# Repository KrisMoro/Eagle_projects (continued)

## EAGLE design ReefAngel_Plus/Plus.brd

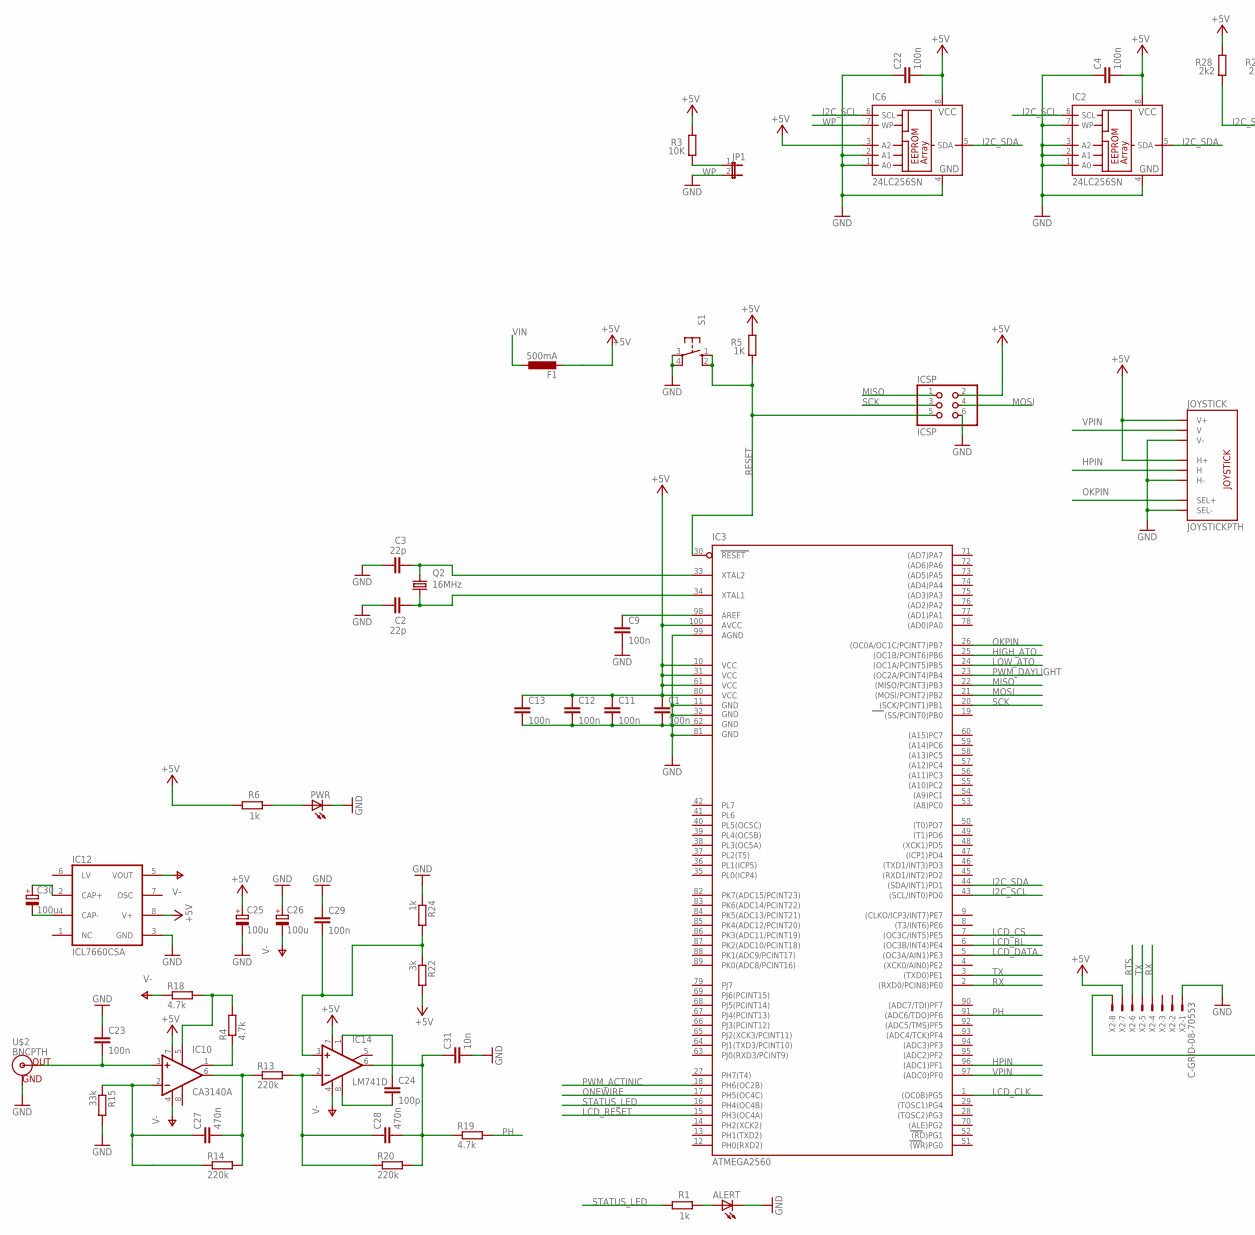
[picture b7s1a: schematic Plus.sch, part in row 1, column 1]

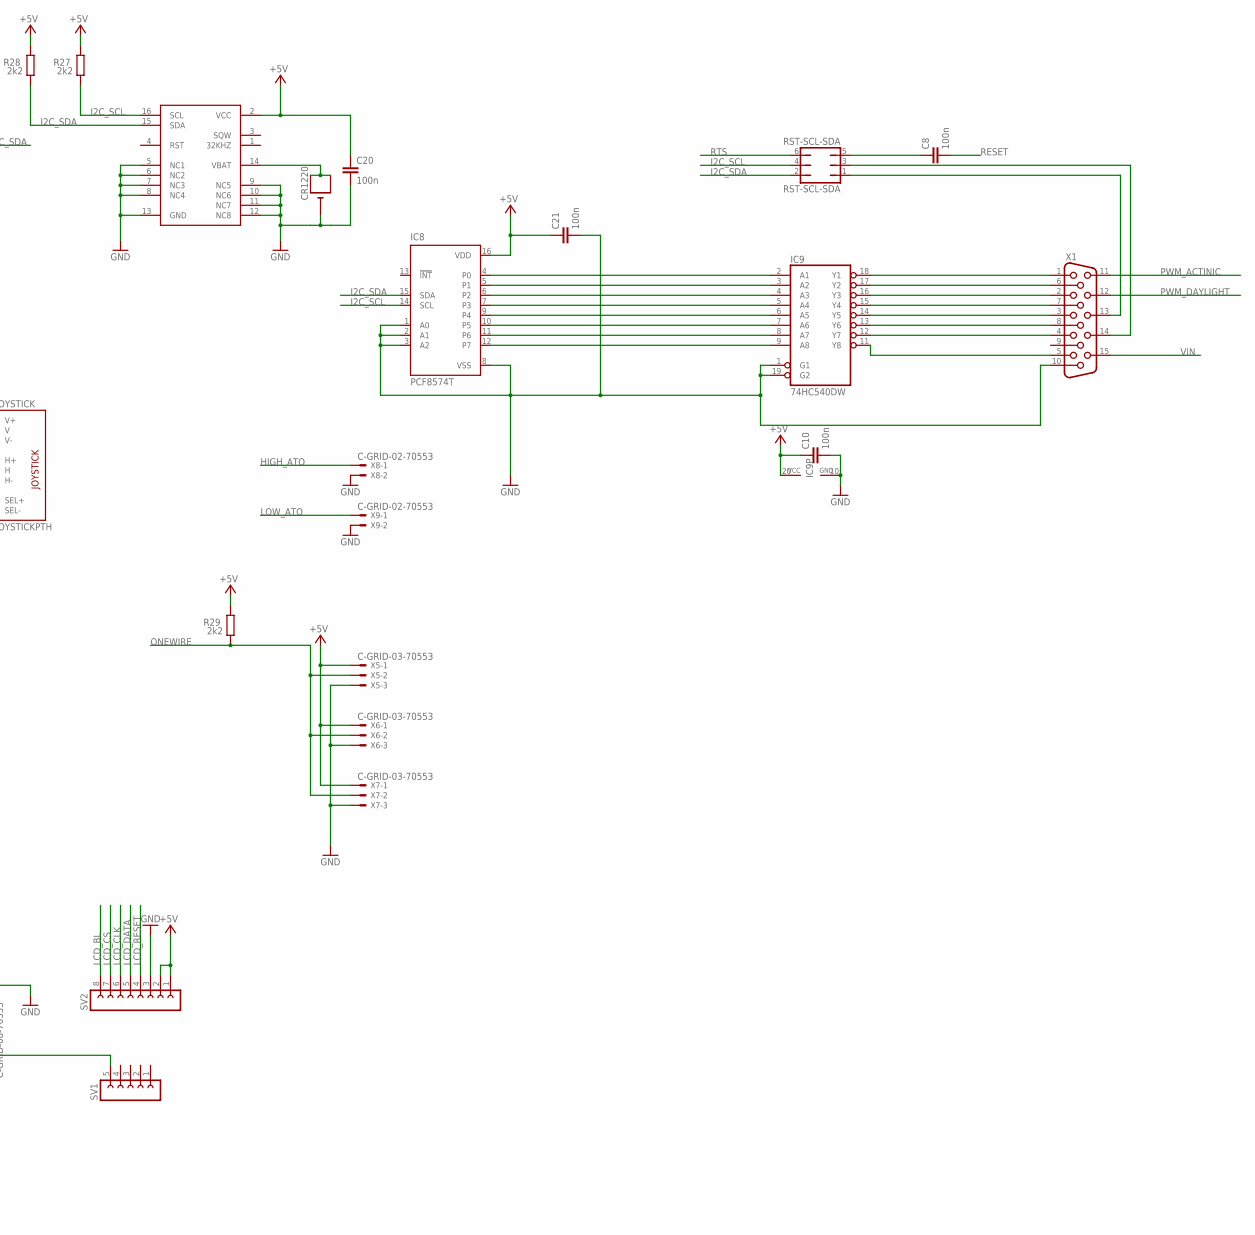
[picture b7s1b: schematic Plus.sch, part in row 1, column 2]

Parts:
ALERT: LED3MM
C1, C4, C8, C9, C10, C11, C12, C13, C20, C21, C22, C23, C29: 100n; C0805
C2, C3: 22p; C0805
C24: 100p; C0805
C25, C26, C30: 100u; PANASONIC_D
C27, C28: 470n; C0805
C31: 10n; C0805
CR1220: CR1220SMT; CR1220-SMD
F1: 500mA; L1812
IC2, IC6: 24LC256SN; SO-08
IC3: ATMEGA2560; TQFP100
IC7: DS3231W; SO16W
IC8: PCF8574T; SO16W
IC9: 74HC540DW; SO20W
IC10: CA3140A; SO08
IC12: ICL7660CSA; SO08
IC14: LM741D; SO08
ICSP: ICSP; 2X03
JOYSTICK: JOYSTICKPTH; JOYSTICK
JP1: JP1E; JP1
PWR: LED3MM
Q2: 16MHz; HC49/S
R1, R6, R24: 1k; R0805
R3: 10K; R0805
R4, R18, R19: 4.7k; R0805
R5: 1K; R0805
R13, R14, R20: 220k; R0805
R15: 33k; R0805
R22: 3k; R0805
R27, R28, R29: 2k2; R0805
RST-SCL-SDA: RST-SCL-SDA; JP3Q
S1: 10-XX; B3F-10XX
SV1: FE05-1
SV2: FE08-1; FE08
U$2: BNCPTH; BNC
X1: HF15H; HDF15H
X2: C-GRID-08-70553; 70553-08
X5, X6, X7: C-GRID-03-70553; 70553-03
X8, X9: C-GRID-02-70553; 70553-02

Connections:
+5V: C1.1, C4.2, C10.1, C11.1, C12.1, C13.1, C20.1, C21.1, C22.2, C25.+, F1.2, IC2.8 (VCC), IC3.10 (VCC), IC3.31 (VCC1), IC3.61 (VCC2), IC3.80 (VCC3), IC3.100 (AVCC), IC6.3 (A2), IC6.8 (VCC), IC7.2 (VCC), IC8.16 (VDD), IC9.20 (VCC), IC10.7 (V+), IC12.8 (V+), IC14.7 (V+), ICSP.2, JOYSTICK.H1 (H+), JOYSTICK.V1 (V+), R3.2, R5.2, R6.1, R22.2, R27.2, R28.2, R29.2, SV2.1, SV2.2, X2.7, X5.1, X6.1, X7.1
GND: ALERT.K (C), C1.2, C2.1, C3.1, C4.1, C9.2, C10.2, C11.2, C12.2, C13.2, C20.2, C21.2, C22.1, C23.1, C25.-, C26.+, C29.1, C31.2, CR1220.-, IC2.1 (A0), IC2.2 (A1), IC2.3 (A2), IC2.4 (GND), IC2.7 (WP), IC3.11 (GND), IC3.32 (GND1), IC3.62 (GND2), IC3.81 (GND3), IC3.99 (AGND), IC6.1 (A0), IC6.2 (A1), IC6.4 (GND), IC7.5 (NC1), IC7.6 (NC2), IC7.7 (NC3), IC7.8 (NC4), IC7.9 (NC5), IC7.10 (NC6), IC7.11 (NC7), IC7.12 (NC8), IC7.13 (GND), IC8.1 (A0), IC8.2 (A1), IC8.3 (A2), IC8.8 (VSS), IC9.1 (G1), IC9.10 (GND), IC9.19 (G2), IC12.3 (GND), ICSP.6, JOYSTICK.B2A (SEL-), JOYSTICK.H3 (H-), JOYSTICK.V3 (V-), JP1.2, PWR.K (C), R15.2, R24.1, S1.3, S1.4 (P1), SV2.3, U$2.GND, X1.10, X2.1, X5.3, X6.3, X7.3, X8.2, X9.2
HIGH_ATO: IC3.25 ((OC1B/PCINT6)PB6), X8.1
HPIN: IC3.96 ((ADC1)PF1), JOYSTICK.H2 (H)
I2C_SCL: IC2.6 (SCL), IC3.43 ((SCL/INT0)PD0), IC6.6 (SCL), IC7.16 (SCL), IC8.14 (SCL), R27.1, RST-SCL-SDA.4
I2C_SDA: IC2.5 (SDA), IC3.44 ((SDA/INT1)PD1), IC6.5 (SDA), IC7.15 (SDA), IC8.15 (SDA), R28.1, RST-SCL-SDA.2
LCD_BL: IC3.6 ((OC3B/INT4)PE4), SV2.8
LCD_CLK: IC3.1 ((OC0B)PG5), SV2.6
LCD_CS: IC3.7 ((OC3C/INT5)PE5), SV2.7
LCD_DATA: IC3.5 ((OC3A/AIN1)PE3), SV2.5
LCD_RESET: IC3.15 (PH3(OC4A)), SV2.4
LOW_ATO: IC3.24 ((OC1A/PCINT5)PB5), X9.1
MISO: IC3.22 ((MISO/PCINT3)PB3), ICSP.1
MOSI: IC3.21 ((MOSI/PCINT2)PB2), ICSP.4
unnamed: C9.1, IC3.98 (AREF)
unnamed: CR1220.+$1 (+), CR1220.+$2 (+1), IC7.14 (VBAT)
unnamed: PWR.A, R6.2
unnamed: C2.2, IC3.34 (XTAL1), Q2.1
unnamed: C3.2, IC3.33 (XTAL2), Q2.2
unnamed: IC9.18 (Y1), X1.1
unnamed: C24.1, IC14.1 (ON1)
unnamed: RST-SCL-SDA.1, X1.13
unnamed: IC9.17 (Y2), X1.6
unnamed: RST-SCL-SDA.3, X1.14
unnamed: IC9.16 (Y3), X1.2
unnamed: IC9.15 (Y4), X1.7
unnamed: IC9.14 (Y5), X1.3
unnamed: IC9.13 (Y6), X1.8
unnamed: IC9.12 (Y7), X1.4
unnamed: IC9.11 (Y8), X1.5
unnamed: IC8.4 (P0), IC9.2 (A1)
unnamed: IC8.5 (P1), IC9.3 (A2)
unnamed: IC8.6 (P2), IC9.4 (A3)
unnamed: IC8.7 (P3), IC9.5 (A4)
unnamed: IC8.9 (P4), IC9.6 (A5)
unnamed: IC8.10 (P5), IC9.7 (A6)
unnamed: IC8.11 (P6), IC9.8 (A7)
unnamed: IC8.12 (P7), IC9.9 (A8)
unnamed: C29.2, IC14.3 (+IN), R22.1, R24.2
unnamed: C30.-, IC12.4 (CAP-)
unnamed: C30.+, IC12.2 (CAP+)
unnamed: C23.2, IC10.3 (+IN), U$2.S (OUT)
unnamed: C24.2, IC14.8 (OPT)
unnamed: C27.2, IC10.6 (OUT), R13.1, R14.2
unnamed: C27.1, IC10.2 (-IN), R14.1, R15.1
unnamed: C8.1, RST-SCL-SDA.5
unnamed: IC10.5 (ON), R4.2, R18.2
unnamed: IC10.1 (ON/CMP), R4.1
unnamed: C28.1, IC14.2 (-IN), R13.2, R20.1
unnamed: C28.2, C31.1, IC14.6 (OUT), R19.1, R20.2
unnamed: ALERT.A, R1.2
unnamed: SV1.5, X2.8
OKPIN: IC3.26 ((OC0A/OC1C/PCINT7)PB7), JOYSTICK.B1A (SEL+)
ONEWIRE: IC3.17 (PH5(OC4C)), R29.1, X5.2, X6.2, X7.2
PH: IC3.91 ((ADC6/TDO)PF6), R19.2
PWM_ACTINIC: IC3.18 (PH6(OC2B)), X1.11
PWM_DAYLIGHT: IC3.23 ((OC2A/PCINT4)PB4), X1.12
RESET: C8.2, IC3.30 (RESET), ICSP.5, R5.1, S1.1 (S), S1.2 (S1)
RTS: RST-SCL-SDA.6, X2.6
RX: IC3.2 ((RXD0/PCIN8)PE0), X2.4
SCK: IC3.20 ((SCK/PCINT1)PB1), ICSP.3
STATUS_LED: IC3.16 (PH4(OC4B)), R1.1
TX: IC3.3 ((TXD0)PE1), X2.5
V-: C26.-, IC10.4 (V-), IC12.5 (VOUT), IC14.4 (V-), R18.1
VIN: F1.1, X1.15
VPIN: IC3.97 ((ADC0)PF0), JOYSTICK.V2 (V)
WP: IC6.7 (WP), JP1.1, R3.1

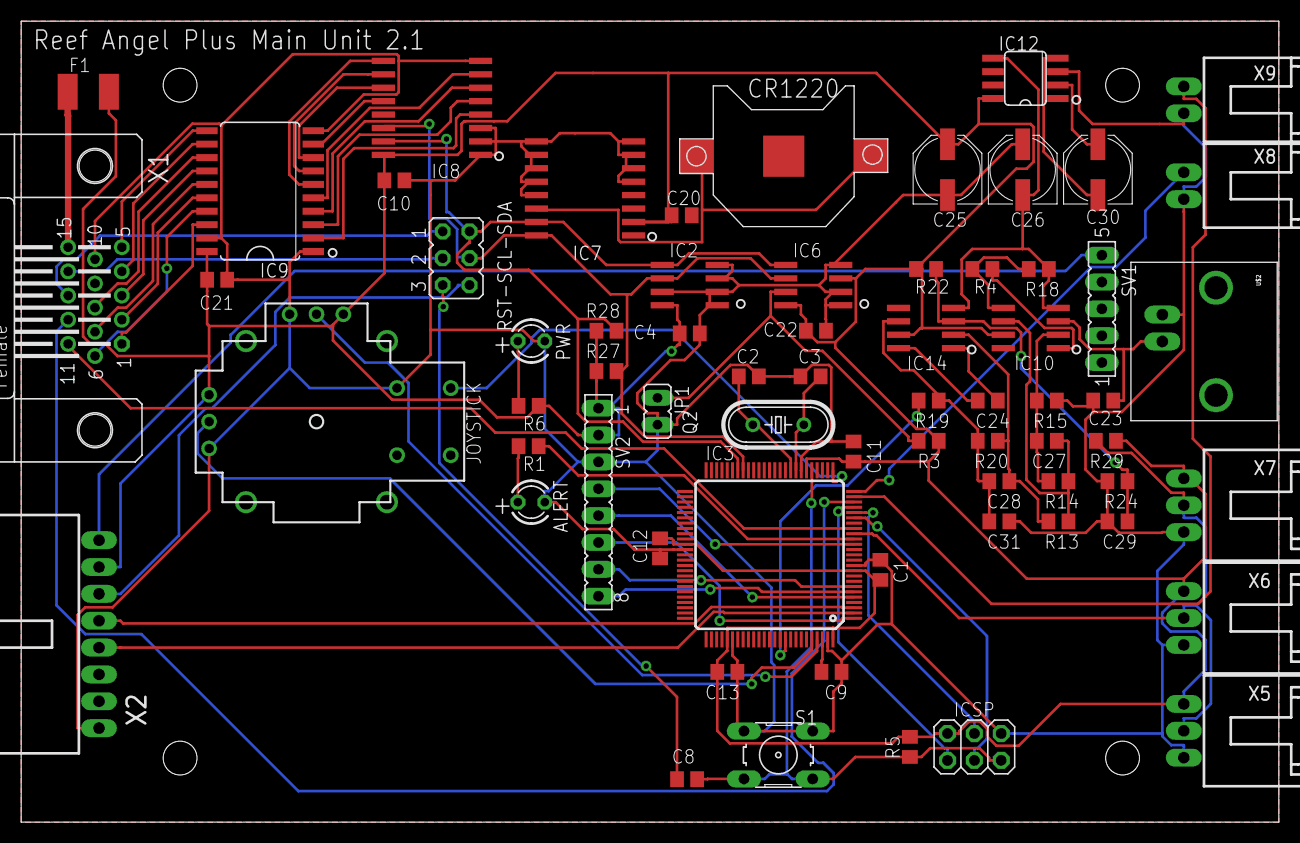
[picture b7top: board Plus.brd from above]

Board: 2 copper layers, 119.0 x 75.8 mm, 67 parts (0 on the bottom side), 67 nets.

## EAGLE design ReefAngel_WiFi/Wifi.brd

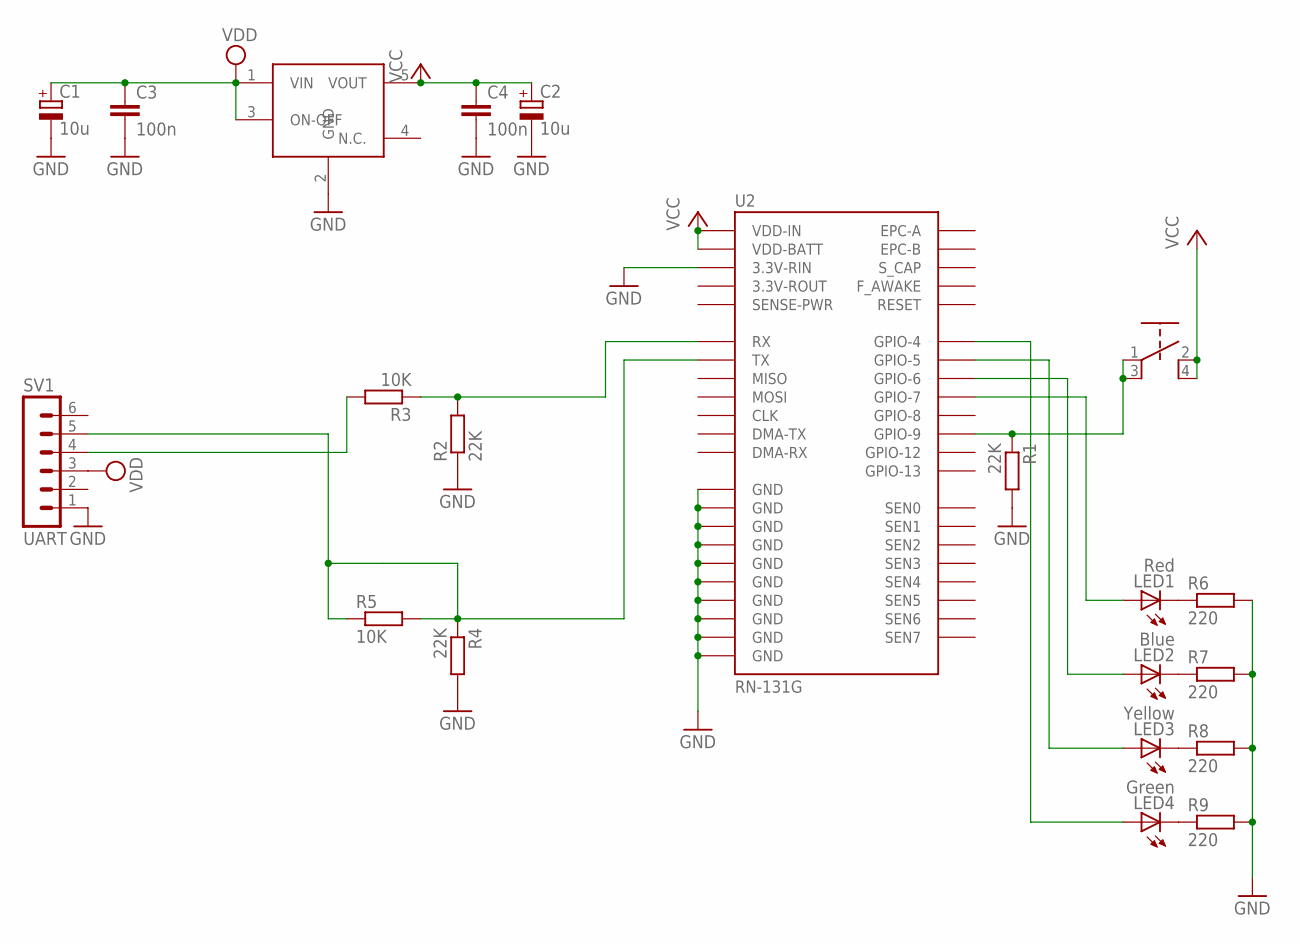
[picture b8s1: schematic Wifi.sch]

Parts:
C1, C2: 10u; A/3216-18W
C3, C4: 100n; C0805
LED1: Red; LED3MM
LED2: Blue; LED3MM
LED3: Yellow; LED3MM
LED4: Green; LED3MM
R1, R2, R4: 22K; R0805
R3, R5: 10K; R0805
R6, R7, R8, R9: 220; R0805
S2: PUSHBUTTON
SV1: UART; MA06-1
U1: LP2985; SOT23-5
U2: RN-131G

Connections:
GND: C1.-, C2.-, C3.2, C4.2, R1.2, R2.1, R4.2, R6.2, R7.2, R8.2, R9.2, SV1.1, U1.2 (GND), U2.P$18 (3.3V-RIN), U2.P$19 (GND), U2.P$36 (GND), U2.P$37 (GND), U2.P$38 (GND), U2.P$39 (GND), U2.P$40 (GND), U2.P$41 (GND), U2.P$42 (GND), U2.P$43 (GND), U2.P$44 (GND)
unnamed: R1.1, S2.1, S2.3, U2.P$24 (GPIO-9)
unnamed: R2.2, R3.1, U2.P$12 (RX)
unnamed: R4.1, R5.1, R5.2, SV1.5, U2.P$13 (TX)
unnamed: LED1.K (C), R6.1
unnamed: R3.2, SV1.4
unnamed: LED2.K (C), R7.1
unnamed: LED3.K (C), R8.1
unnamed: LED4.K (C), R9.1
unnamed: LED1.A, U2.P$26 (GPIO-7)
unnamed: LED2.A, U2.P$27 (GPIO-6)
unnamed: LED3.A, U2.P$28 (GPIO-5)
unnamed: LED4.A, U2.P$29 (GPIO-4)
VCC: C2.+, C4.1, S2.2, S2.4, U1.5 (VOUT), U2.P$20 (VDD-BATT), U2.P$21 (VDD-IN)
VDD: C1.+, C3.1, SV1.3, U1.1 (VIN), U1.3 (ON-OFF)

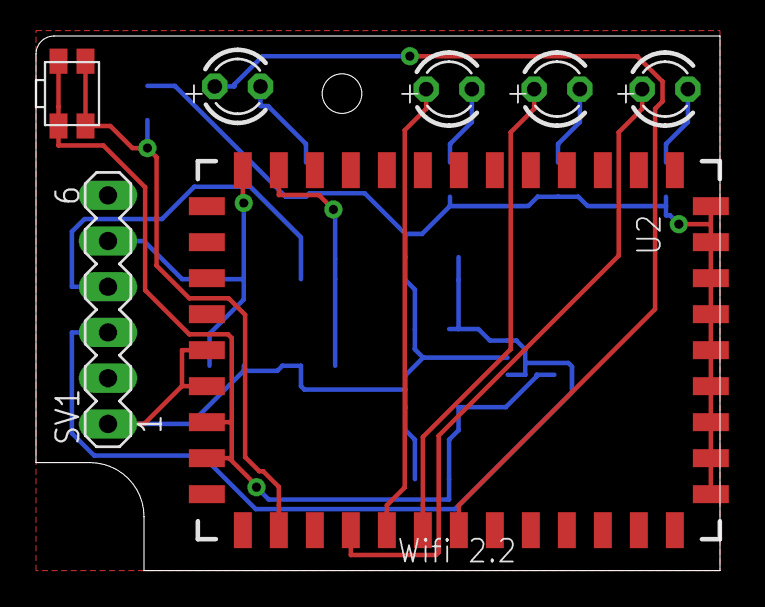
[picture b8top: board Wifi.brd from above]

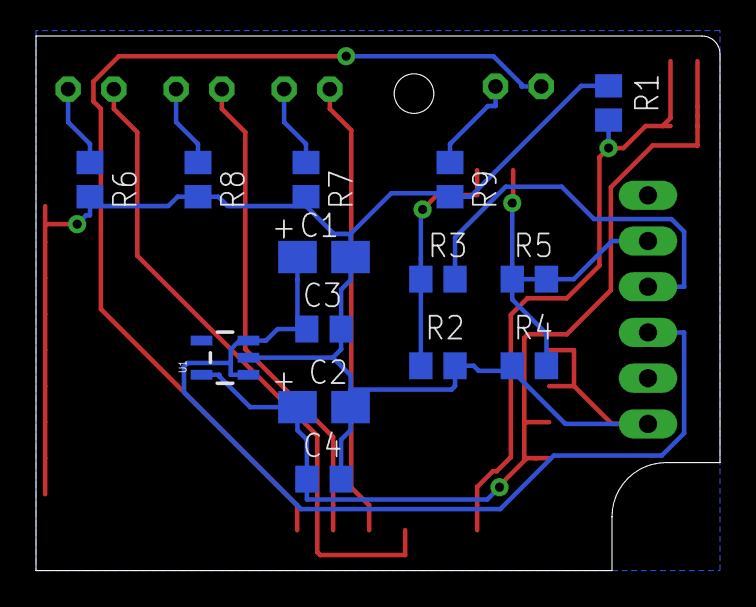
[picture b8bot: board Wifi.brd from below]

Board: 2 copper layers, 38.0 x 29.7 mm, 21 parts (14 on the bottom side), 15 nets.

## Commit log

2018-06-24 Initial migration from OneDrive
2019-09-12 TLE5010 added, folders cleanup
2019-09-13 TLE5010.brd fixed
2019-09-14 Flatcam bat file added
